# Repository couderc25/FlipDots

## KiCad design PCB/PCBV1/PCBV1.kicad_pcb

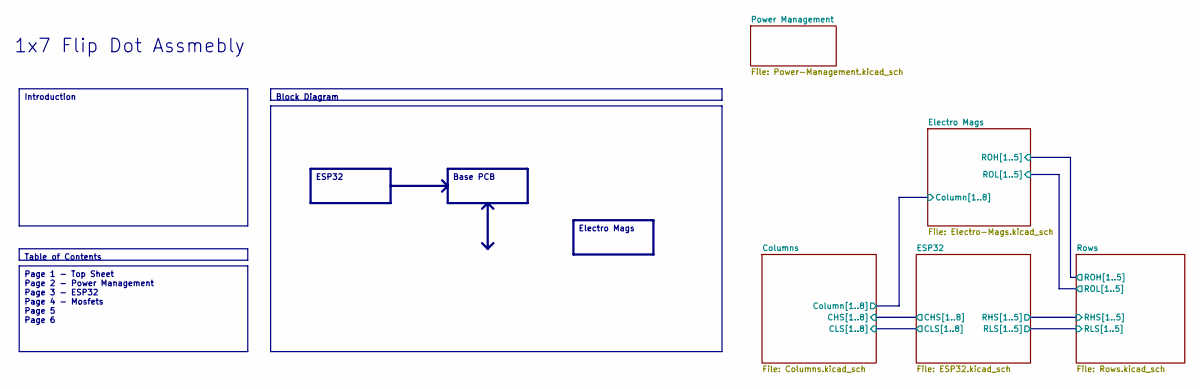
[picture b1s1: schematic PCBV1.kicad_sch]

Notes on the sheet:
Electro Mags
Block Diagram
Base PCB
Page 1 - Top Sheet Page 2 - Power Management Page 3 - ESP32 Page 4 - Mosfets Page 5 Page 6
Table of Contents
ESP32
Introduction
1x7 Flip Dot Assmebly

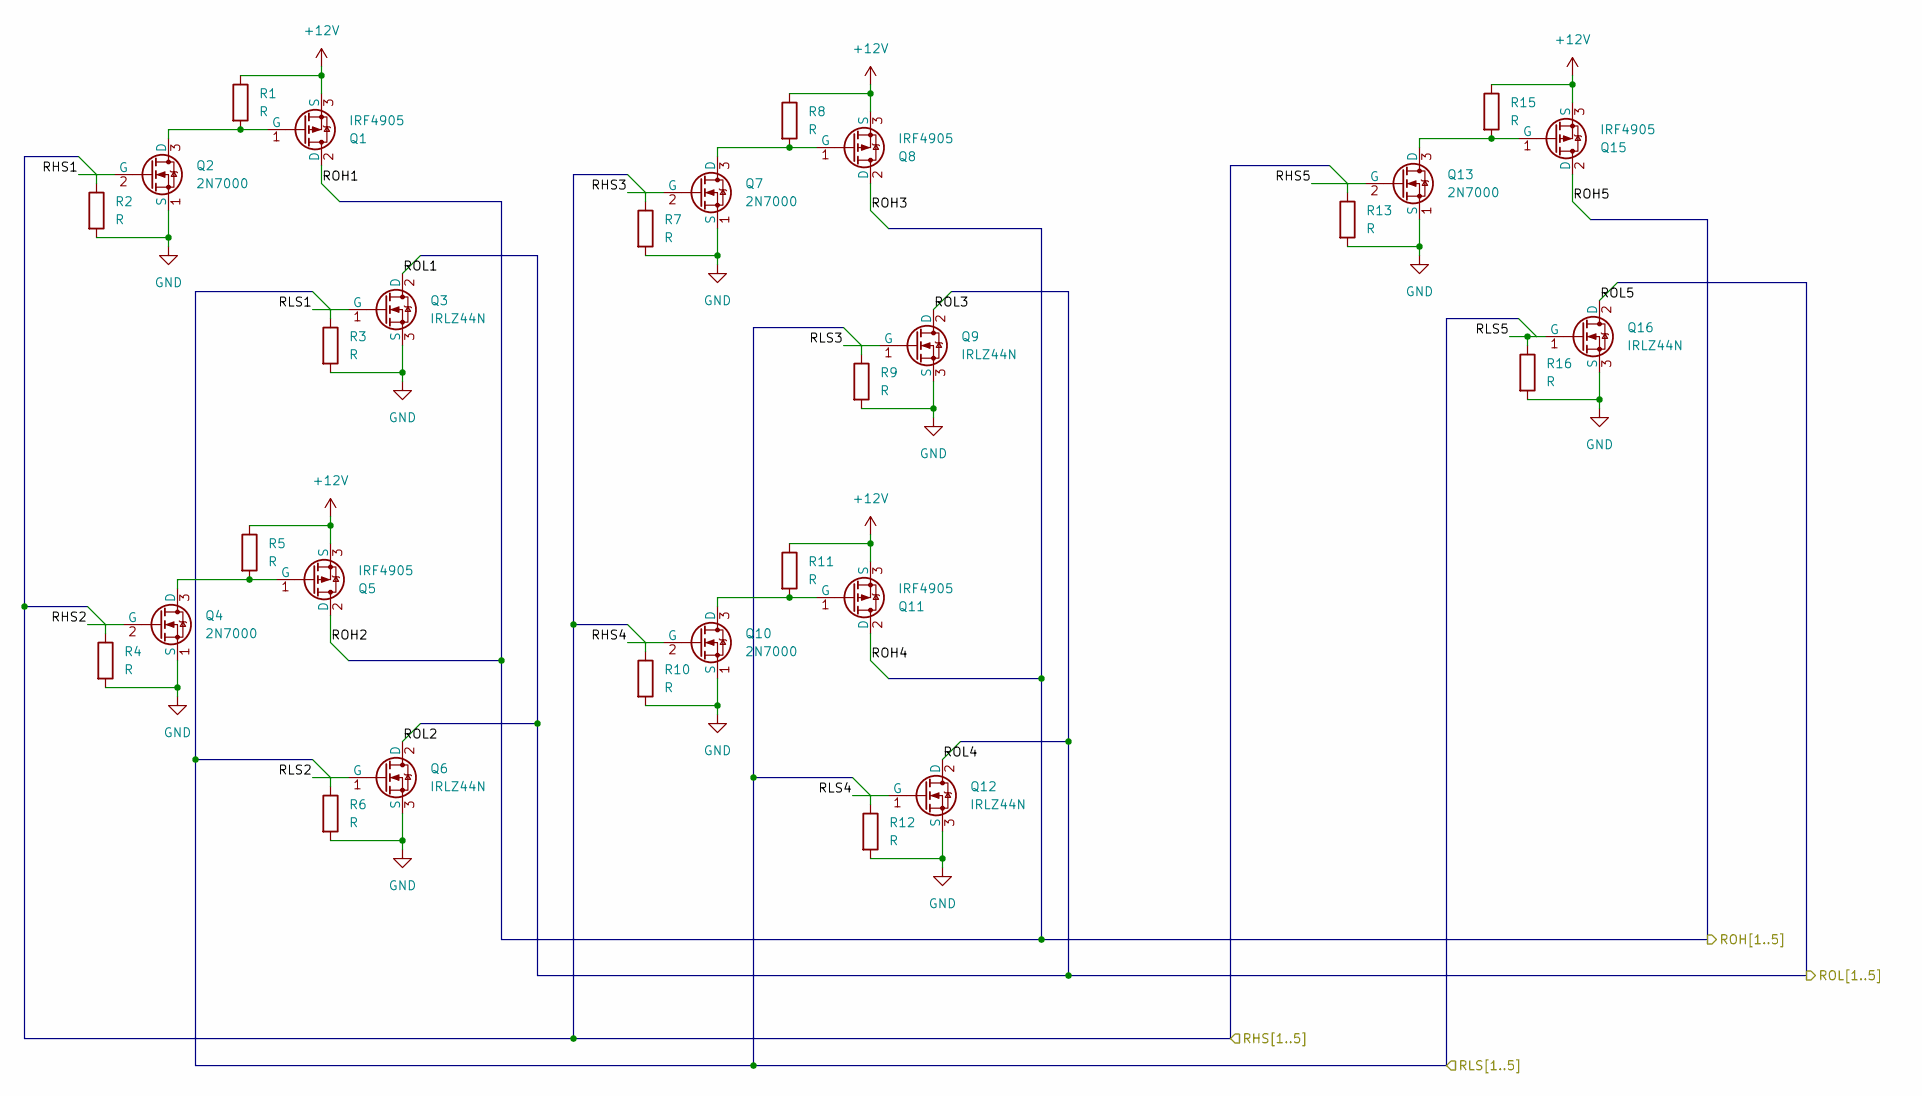
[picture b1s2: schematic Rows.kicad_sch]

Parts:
Q1, Q5, Q8, Q11, Q15: IRF4905; TO-220-3_Vertical
Q2, Q4, Q7, Q10, Q13: 2N7000; TO-92_Inline
Q3, Q6, Q9, Q12, Q16: IRLZ44N; TO-220-3_Vertical
R1, R2, R3, R4, R5, R6, R7, R8, R9, R10, R11, R12, R13, R15, R16: R; R_Axial_DIN0411_L9.9mm_D3.6mm_P15.24mm_Horizontal

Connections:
+12V: Q1.3 (S), Q5.3 (S), Q8.3 (S), Q11.3 (S), Q15.3 (S), R1.1, R5.1, R8.1, R11.1, R15.1; also elsewhere on the board
/ESP32/RHS1: Q2.2 (G), R2.1; also elsewhere on the board
/ESP32/RHS2: Q4.2 (G), R4.1; also elsewhere on the board
/ESP32/RHS3: Q7.2 (G), R7.1; also elsewhere on the board
/ESP32/RHS4: Q10.2 (G), R10.1; also elsewhere on the board
/ESP32/RHS5: Q13.2 (G), R13.1; also elsewhere on the board
/ESP32/RLS1: Q3.1 (G), R3.1; also elsewhere on the board
/ESP32/RLS2: Q6.1 (G), R6.1; also elsewhere on the board
/ESP32/RLS3: Q9.1 (G), R9.1; also elsewhere on the board
/ESP32/RLS4: Q12.1 (G), R12.1; also elsewhere on the board
/ESP32/RLS5: Q16.1 (G), R16.1; also elsewhere on the board
/Electro Mags/ROH1: Q1.2 (D); also elsewhere on the board
/Electro Mags/ROH2: Q5.2 (D); also elsewhere on the board
/Electro Mags/ROH3: Q8.2 (D); also elsewhere on the board
/Electro Mags/ROH4: Q11.2 (D); also elsewhere on the board
/Electro Mags/ROH5: Q15.2 (D); also elsewhere on the board
/Electro Mags/ROL1: Q3.2 (D); also elsewhere on the board
/Electro Mags/ROL2: Q6.2 (D); also elsewhere on the board
/Electro Mags/ROL3: Q9.2 (D); also elsewhere on the board
/Electro Mags/ROL4: Q12.2 (D); also elsewhere on the board
/Electro Mags/ROL5: Q16.2 (D); also elsewhere on the board
unnamed: Q1.1 (G), Q2.3 (D), R1.2
unnamed: Q4.3 (D), Q5.1 (G), R5.2
unnamed: Q7.3 (D), Q8.1 (G), R8.2
unnamed: Q10.3 (D), Q11.1 (G), R11.2
unnamed: Q13.3 (D), Q15.1 (G), R15.2

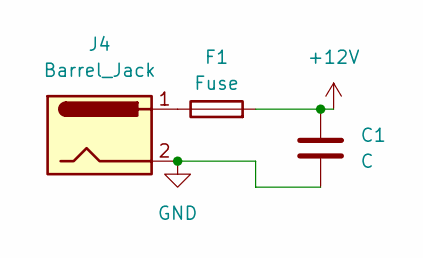
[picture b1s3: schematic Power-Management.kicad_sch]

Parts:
C1: C
F1: Fuse; Fuseholder_Clip-5x20mm_Littelfuse_111_Inline_P20.00x5.00mm_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
J4: Barrel_Jack; BarrelJack_Horizontal

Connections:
+12V: C1.1, F1.2; also elsewhere on the board
unnamed: F1.1, J4.1

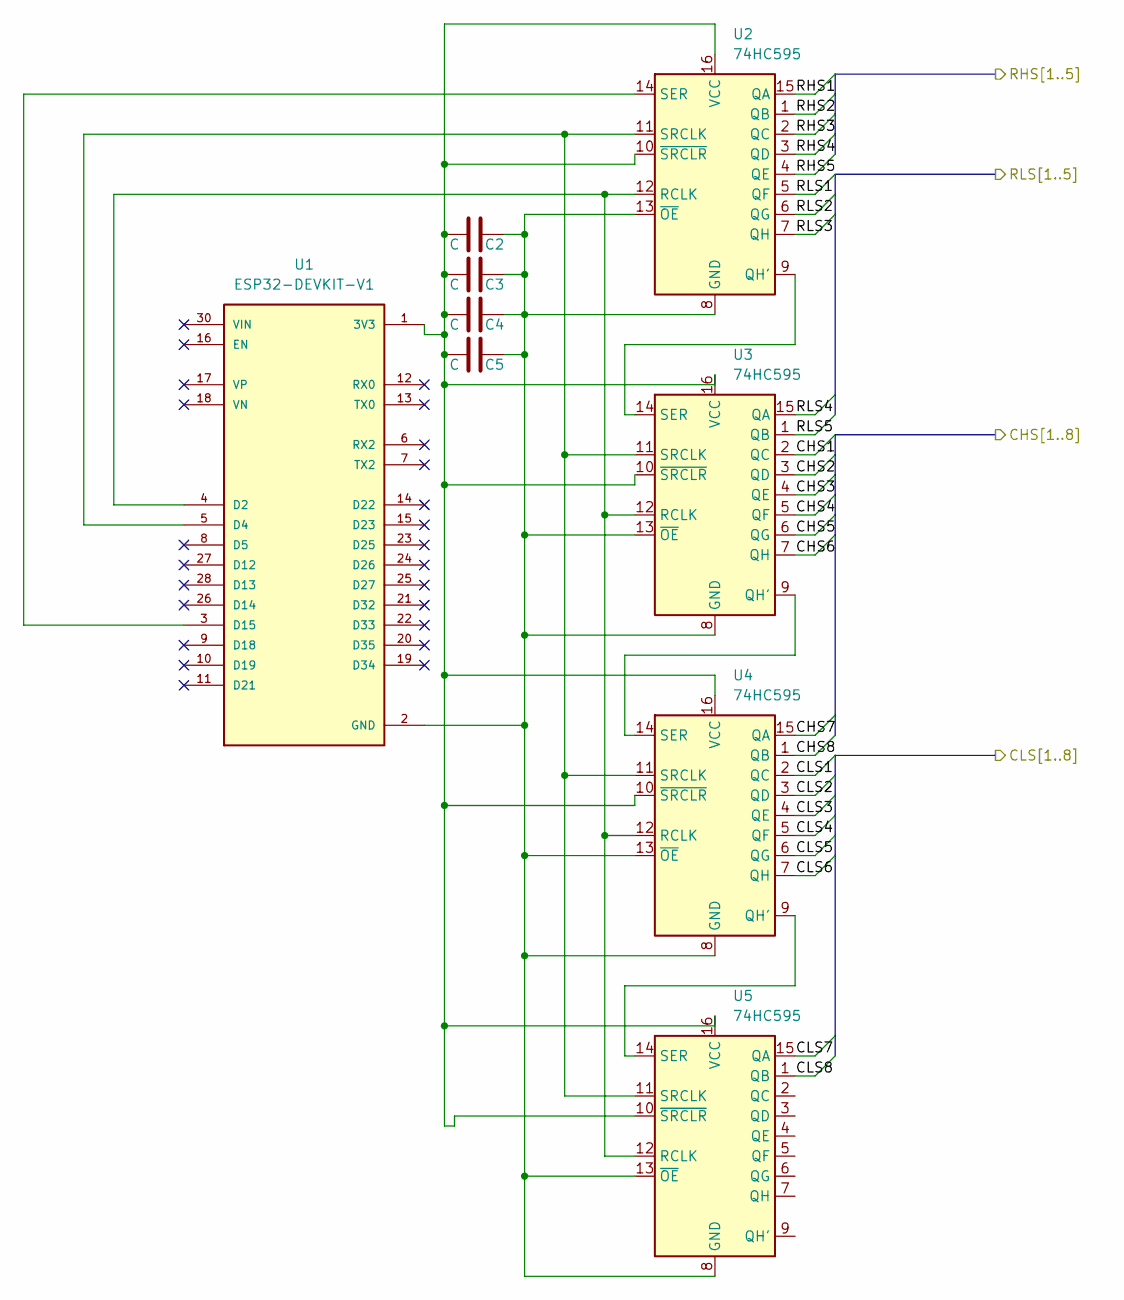
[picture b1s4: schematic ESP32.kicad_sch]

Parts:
C2, C3, C4, C5: C; C_Disc_D5.0mm_W2.5mm_P5.00mm
U1: ESP32-DEVKIT-V1; MODULE_ESP32_DEVKIT_V1; MPN ESP32-DEVKIT-V1
U2, U3, U4, U5: 74HC595; DIP-16_W7.62mm_Socket_LongPads

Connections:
/Columns/CHS1: U3.2 (QC); also elsewhere on the board
/Columns/CHS2: U3.3 (QD); also elsewhere on the board
/Columns/CHS3: U3.4 (QE); also elsewhere on the board
/Columns/CHS4: U3.5 (QF); also elsewhere on the board
/Columns/CHS5: U3.6 (QG); also elsewhere on the board
/Columns/CHS6: U3.7 (QH); also elsewhere on the board
/Columns/CHS7: U4.15 (QA); also elsewhere on the board
/Columns/CHS8: U4.1 (QB); also elsewhere on the board
/Columns/CLS1: U4.2 (QC); also elsewhere on the board
/Columns/CLS2: U4.3 (QD); also elsewhere on the board
/Columns/CLS3: U4.4 (QE); also elsewhere on the board
/Columns/CLS4: U4.5 (QF); also elsewhere on the board
/Columns/CLS5: U4.6 (QG); also elsewhere on the board
/Columns/CLS6: U4.7 (QH); also elsewhere on the board
/Columns/CLS7: U5.15 (QA); also elsewhere on the board
/Columns/CLS8: U5.1 (QB); also elsewhere on the board
/ESP32/RHS1: U2.15 (QA); also elsewhere on the board
/ESP32/RHS2: U2.1 (QB); also elsewhere on the board
/ESP32/RHS3: U2.2 (QC); also elsewhere on the board
/ESP32/RHS4: U2.3 (QD); also elsewhere on the board
/ESP32/RHS5: U2.4 (QE); also elsewhere on the board
/ESP32/RLS1: U2.5 (QF); also elsewhere on the board
/ESP32/RLS2: U2.6 (QG); also elsewhere on the board
/ESP32/RLS3: U2.7 (QH); also elsewhere on the board
/ESP32/RLS4: U3.15 (QA); also elsewhere on the board
/ESP32/RLS5: U3.1 (QB); also elsewhere on the board
unnamed: C2.1, C3.1, C4.1, C5.1, U1.1 (3V3), U2.10 (~SRCLR), U2.16 (VCC), U3.10 (~SRCLR), U3.16 (VCC), U4.10 (~SRCLR), U4.16 (VCC), U5.10 (~SRCLR), U5.16 (VCC)
unnamed: U1.4 (D2), U2.12 (RCLK), U3.12 (RCLK), U4.12 (RCLK), U5.12 (RCLK)
unnamed: U1.5 (D4), U2.11 (SRCLK), U3.11 (SRCLK), U4.11 (SRCLK), U5.11 (SRCLK)
unnamed: U1.3 (D15), U2.14 (SER)
unnamed: U2.9 (QH'), U3.14 (SER)
unnamed: U3.9 (QH'), U4.14 (SER)
unnamed: U4.9 (QH'), U5.14 (SER)

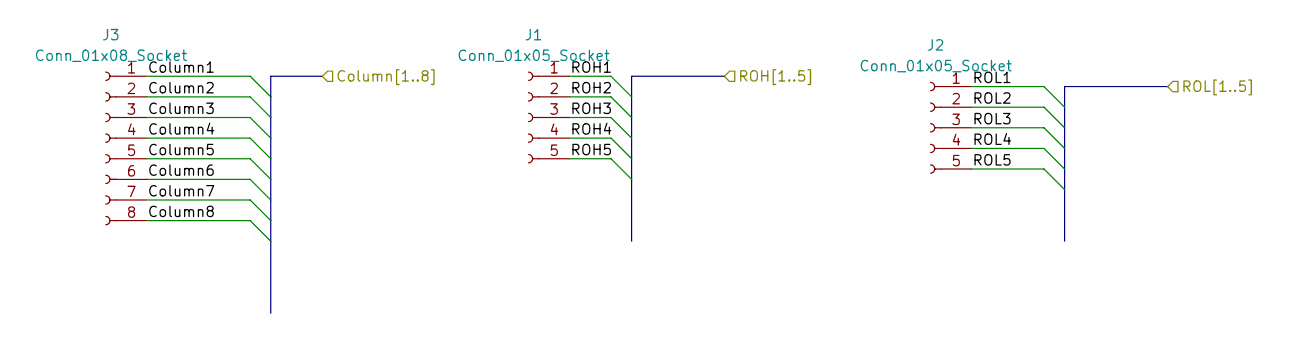
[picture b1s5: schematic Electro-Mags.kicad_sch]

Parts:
J1, J2: Conn_01x05_Socket; PinHeader_1x05_P2.54mm_Vertical
J3: Conn_01x08_Socket; PinHeader_1x08_P2.54mm_Vertical

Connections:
/Columns/Column1: J3.1; also elsewhere on the board
/Columns/Column2: J3.2; also elsewhere on the board
/Columns/Column3: J3.3; also elsewhere on the board
/Columns/Column4: J3.4; also elsewhere on the board
/Columns/Column5: J3.5; also elsewhere on the board
/Columns/Column6: J3.6; also elsewhere on the board
/Columns/Column7: J3.7; also elsewhere on the board
/Columns/Column8: J3.8; also elsewhere on the board
/Electro Mags/ROH1: J1.1; also elsewhere on the board
/Electro Mags/ROH2: J1.2; also elsewhere on the board
/Electro Mags/ROH3: J1.3; also elsewhere on the board
/Electro Mags/ROH4: J1.4; also elsewhere on the board
/Electro Mags/ROH5: J1.5; also elsewhere on the board
/Electro Mags/ROL1: J2.1; also elsewhere on the board
/Electro Mags/ROL2: J2.2; also elsewhere on the board
/Electro Mags/ROL3: J2.3; also elsewhere on the board
/Electro Mags/ROL4: J2.4; also elsewhere on the board
/Electro Mags/ROL5: J2.5; also elsewhere on the board

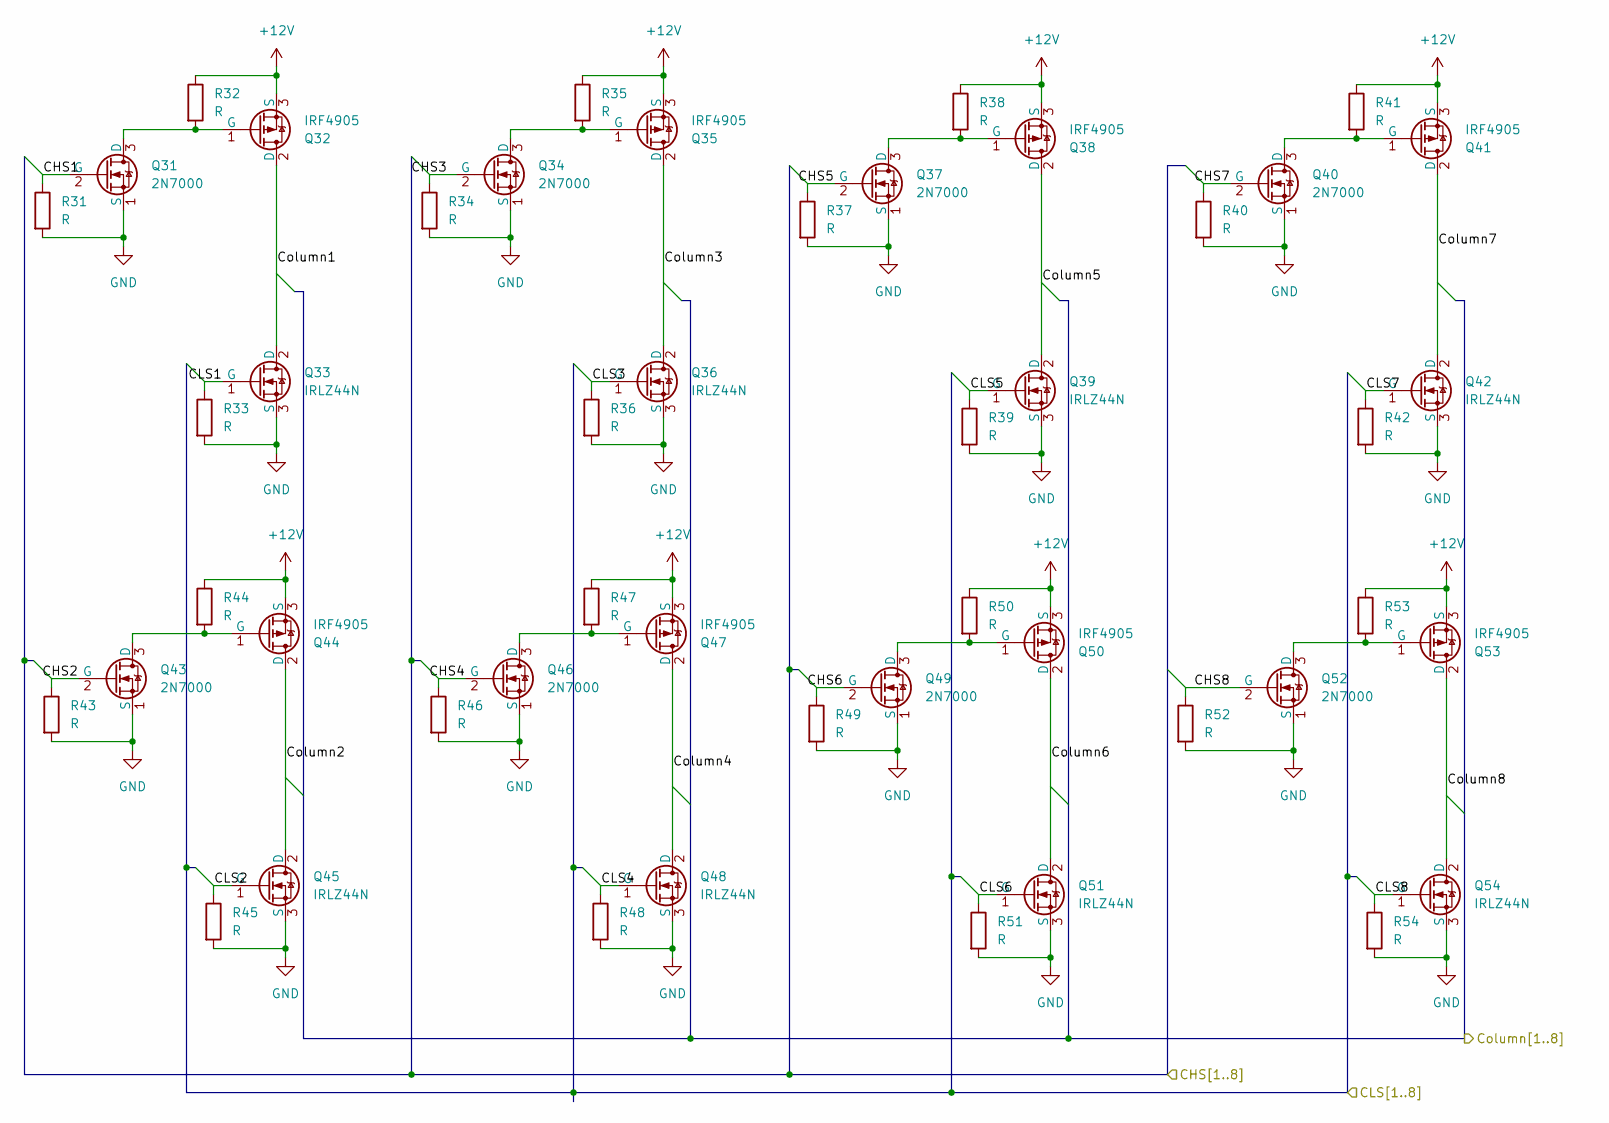
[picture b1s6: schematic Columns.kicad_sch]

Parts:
Q31, Q34, Q37, Q40, Q43, Q46, Q49, Q52: 2N7000; TO-92_Inline
Q32, Q35, Q38, Q41, Q44, Q47, Q50, Q53: IRF4905; TO-220-3_Vertical
Q33, Q36, Q39, Q42, Q45, Q48, Q51, Q54: IRLZ44N; TO-220-3_Vertical
R31, R32, R33, R34, R35, R36, R37, R38, R39, R40, R41, R42, R43, R44, R45, R46, R47, R48, R49, R50, R51, R52, R53, R54: R; R_Axial_DIN0411_L9.9mm_D3.6mm_P15.24mm_Horizontal

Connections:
+12V: Q32.3 (S), Q35.3 (S), Q38.3 (S), Q41.3 (S), Q44.3 (S), Q47.3 (S), Q50.3 (S), Q53.3 (S), R32.1, R35.1, R38.1, R41.1, R44.1, R47.1, R50.1, R53.1; also elsewhere on the board
/Columns/CHS1: Q31.2 (G), R31.1; also elsewhere on the board
/Columns/CHS2: Q43.2 (G), R43.1; also elsewhere on the board
/Columns/CHS3: Q34.2 (G), R34.1; also elsewhere on the board
/Columns/CHS4: Q46.2 (G), R46.1; also elsewhere on the board
/Columns/CHS5: Q37.2 (G), R37.1; also elsewhere on the board
/Columns/CHS6: Q49.2 (G), R49.1; also elsewhere on the board
/Columns/CHS7: Q40.2 (G), R40.1; also elsewhere on the board
/Columns/CHS8: Q52.2 (G), R52.1; also elsewhere on the board
/Columns/CLS1: Q33.1 (G), R33.1; also elsewhere on the board
/Columns/CLS2: Q45.1 (G), R45.1; also elsewhere on the board
/Columns/CLS3: Q36.1 (G), R36.1; also elsewhere on the board
/Columns/CLS4: Q48.1 (G), R48.1; also elsewhere on the board
/Columns/CLS5: Q39.1 (G), R39.1; also elsewhere on the board
/Columns/CLS6: Q51.1 (G), R51.1; also elsewhere on the board
/Columns/CLS7: Q42.1 (G), R42.1; also elsewhere on the board
/Columns/CLS8: Q54.1 (G), R54.1; also elsewhere on the board
/Columns/Column1: Q32.2 (D), Q33.2 (D); also elsewhere on the board
/Columns/Column2: Q44.2 (D), Q45.2 (D); also elsewhere on the board
/Columns/Column3: Q35.2 (D), Q36.2 (D); also elsewhere on the board
/Columns/Column4: Q47.2 (D), Q48.2 (D); also elsewhere on the board
/Columns/Column5: Q38.2 (D), Q39.2 (D); also elsewhere on the board
/Columns/Column6: Q50.2 (D), Q51.2 (D); also elsewhere on the board
/Columns/Column7: Q41.2 (D), Q42.2 (D); also elsewhere on the board
/Columns/Column8: Q53.2 (D), Q54.2 (D); also elsewhere on the board
unnamed: Q31.3 (D), Q32.1 (G), R32.2
unnamed: Q34.3 (D), Q35.1 (G), R35.2
unnamed: Q37.3 (D), Q38.1 (G), R38.2
unnamed: Q40.3 (D), Q41.1 (G), R41.2
unnamed: Q43.3 (D), Q44.1 (G), R44.2
unnamed: Q46.3 (D), Q47.1 (G), R47.2
unnamed: Q49.3 (D), Q50.1 (G), R50.2
unnamed: Q52.3 (D), Q53.1 (G), R53.2

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
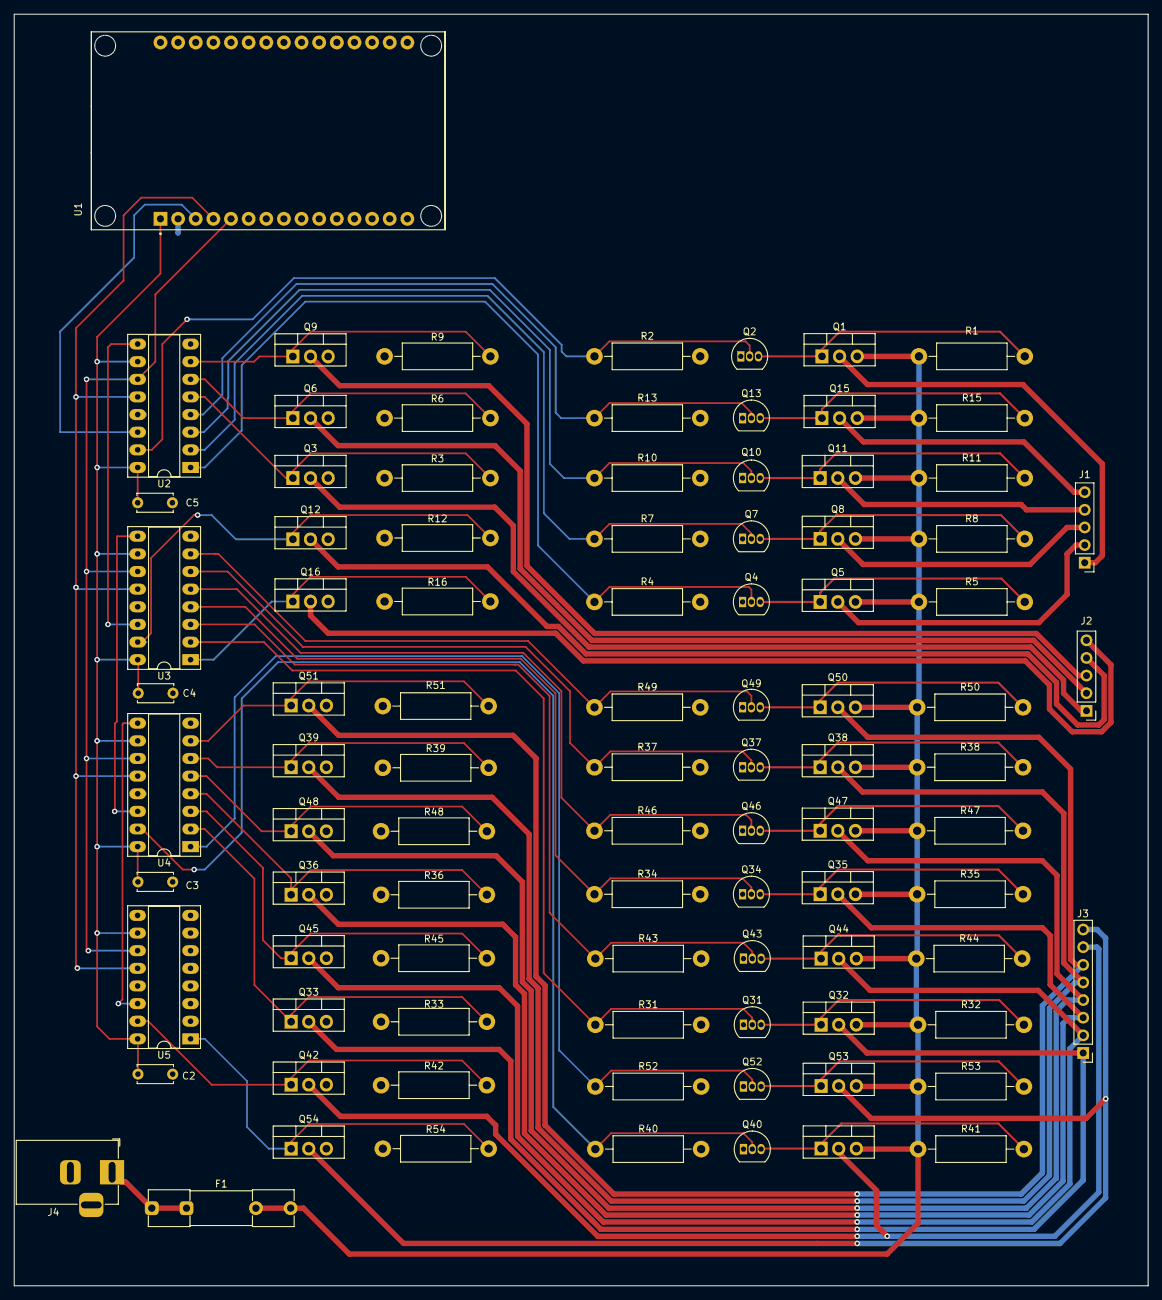
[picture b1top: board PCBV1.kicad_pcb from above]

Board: 2 copper layers, 163.3 x 183.1 mm, 92 parts (0 on the bottom side), 67 nets.
